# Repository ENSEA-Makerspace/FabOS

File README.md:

# FabOS
FabLab Operating System

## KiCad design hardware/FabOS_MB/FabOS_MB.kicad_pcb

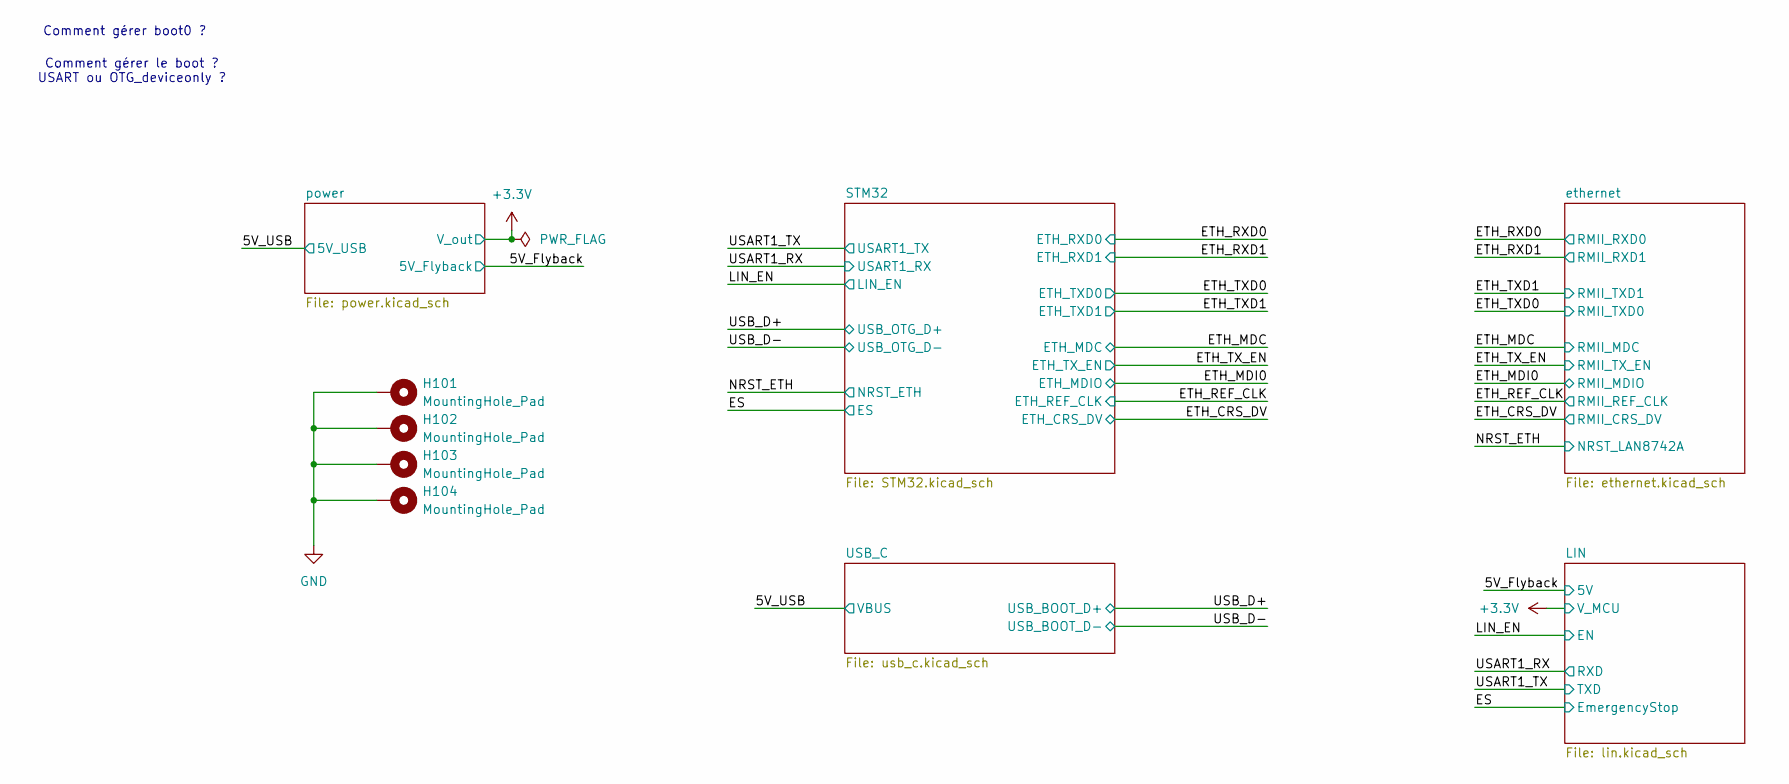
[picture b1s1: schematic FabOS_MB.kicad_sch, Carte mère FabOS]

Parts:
H101, H102, H103, H104: MountingHole_Pad; MountingHole_3.2mm_M3_Pad_Via

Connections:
GND: H101.1, H102.1, H103.1, H104.1; also elsewhere on the board

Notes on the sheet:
Comment gérer boot0 ?
Comment gérer le boot ? USART ou OTG_deviceonly ?

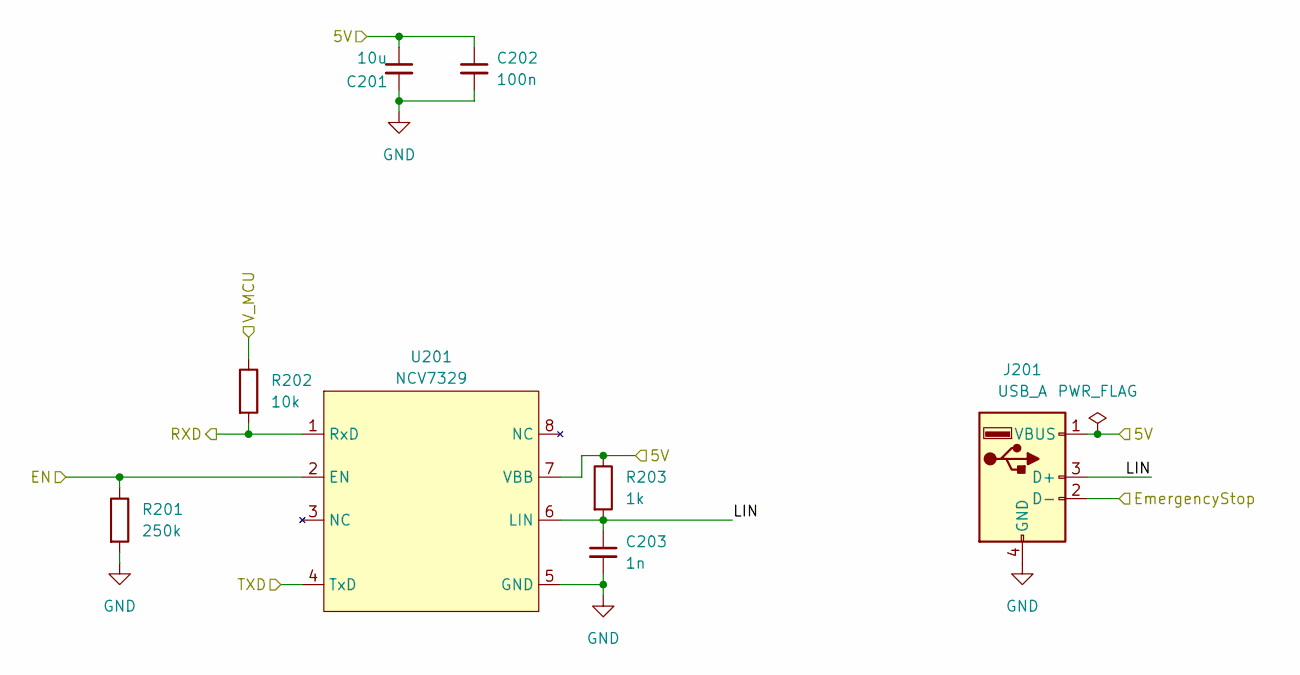
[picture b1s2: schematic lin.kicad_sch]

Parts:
C201: 10u; C_0402_1005Metric; MPN CL05A106MQ5NUNC; LCSC C15525
C202: 100n; C_0402_1005Metric; LCSC C361203
C203: 1n; C_0402_1005Metric; LCSC C92841
J201: USB_A; USB_A_Femelle; MPN 908-371A1011D10100; LCSC C42576
R201: 250k; R_0402_1005Metric; LCSC C409682
R202: 10k; R_0402_1005Metric; LCSC C25744
R203: 1k; R_0402_1005Metric; LCSC C102748
U201: NCV7329; MPN NCV7329D10R2G; LCSC C194435

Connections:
+3.3V: R202.1; also elsewhere on the board
/5V_Flyback: C201.1, C202.1, J201.1 (VBUS), R203.1, U201.7 (VBB); also elsewhere on the board
/ES: J201.2 (D-); also elsewhere on the board
/LIN/LIN: C203.1, J201.3 (D+), R203.2, U201.6 (LIN)
/LIN_EN: R201.1, U201.2 (EN); also elsewhere on the board
/USART1_RX: R202.2, U201.1 (RxD); also elsewhere on the board
/USART1_TX: U201.4 (TxD); also elsewhere on the board
GND: C201.2, C202.2, C203.2, J201.4 (GND), R201.2, U201.5 (GND); also elsewhere on the board

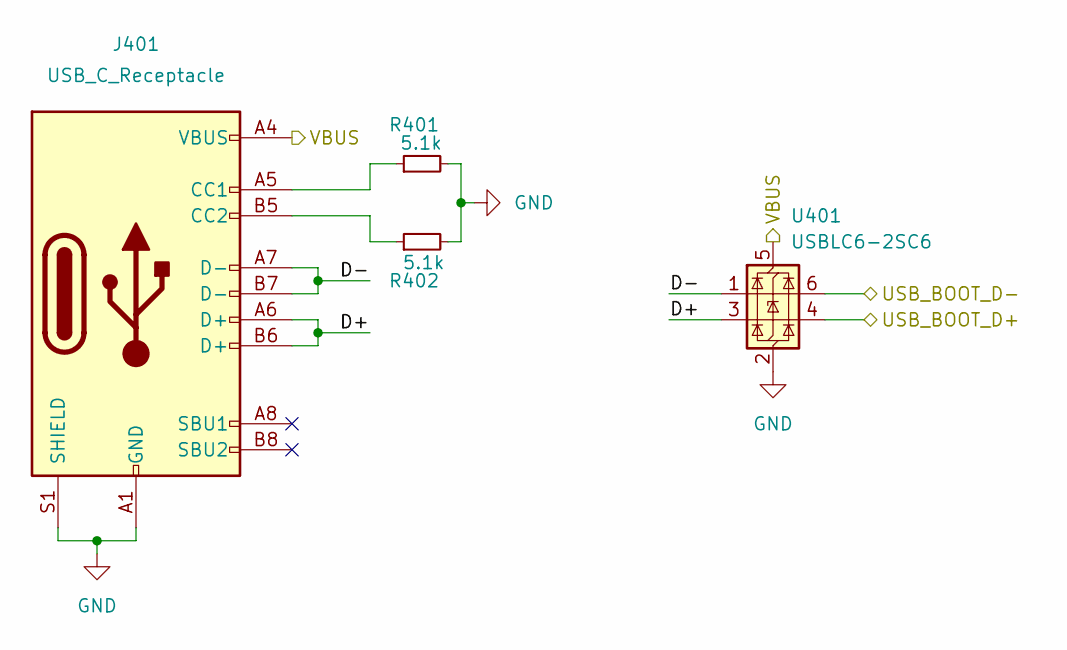
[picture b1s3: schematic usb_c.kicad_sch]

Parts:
J401: USB_C_Receptacle; USB_C_femelle_12P; MPN MC-311D; LCSC C136423
R401, R402: 5.1k; R_0402_1005Metric; LCSC C25905
U401: USBLC6-2SC6; SOT-23-6; LCSC C2827654

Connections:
/5V_USB: J401.A4 (VBUS), U401.5 (VBUS); also elsewhere on the board
/USB_C/D+: J401.A6 (D+), J401.B6 (D+), U401.3 (I/O2)
/USB_C/D-: J401.A7 (D-), J401.B7 (D-), U401.1 (I/O1)
/USB_D+: U401.4 (I/O2); also elsewhere on the board
/USB_D-: U401.6 (I/O1); also elsewhere on the board
GND: J401.A1 (GND), J401.S1 (SHIELD), R401.2, R402.2, U401.2 (GND); also elsewhere on the board
unnamed: J401.A5 (CC1), R401.1
unnamed: J401.B5 (CC2), R402.1

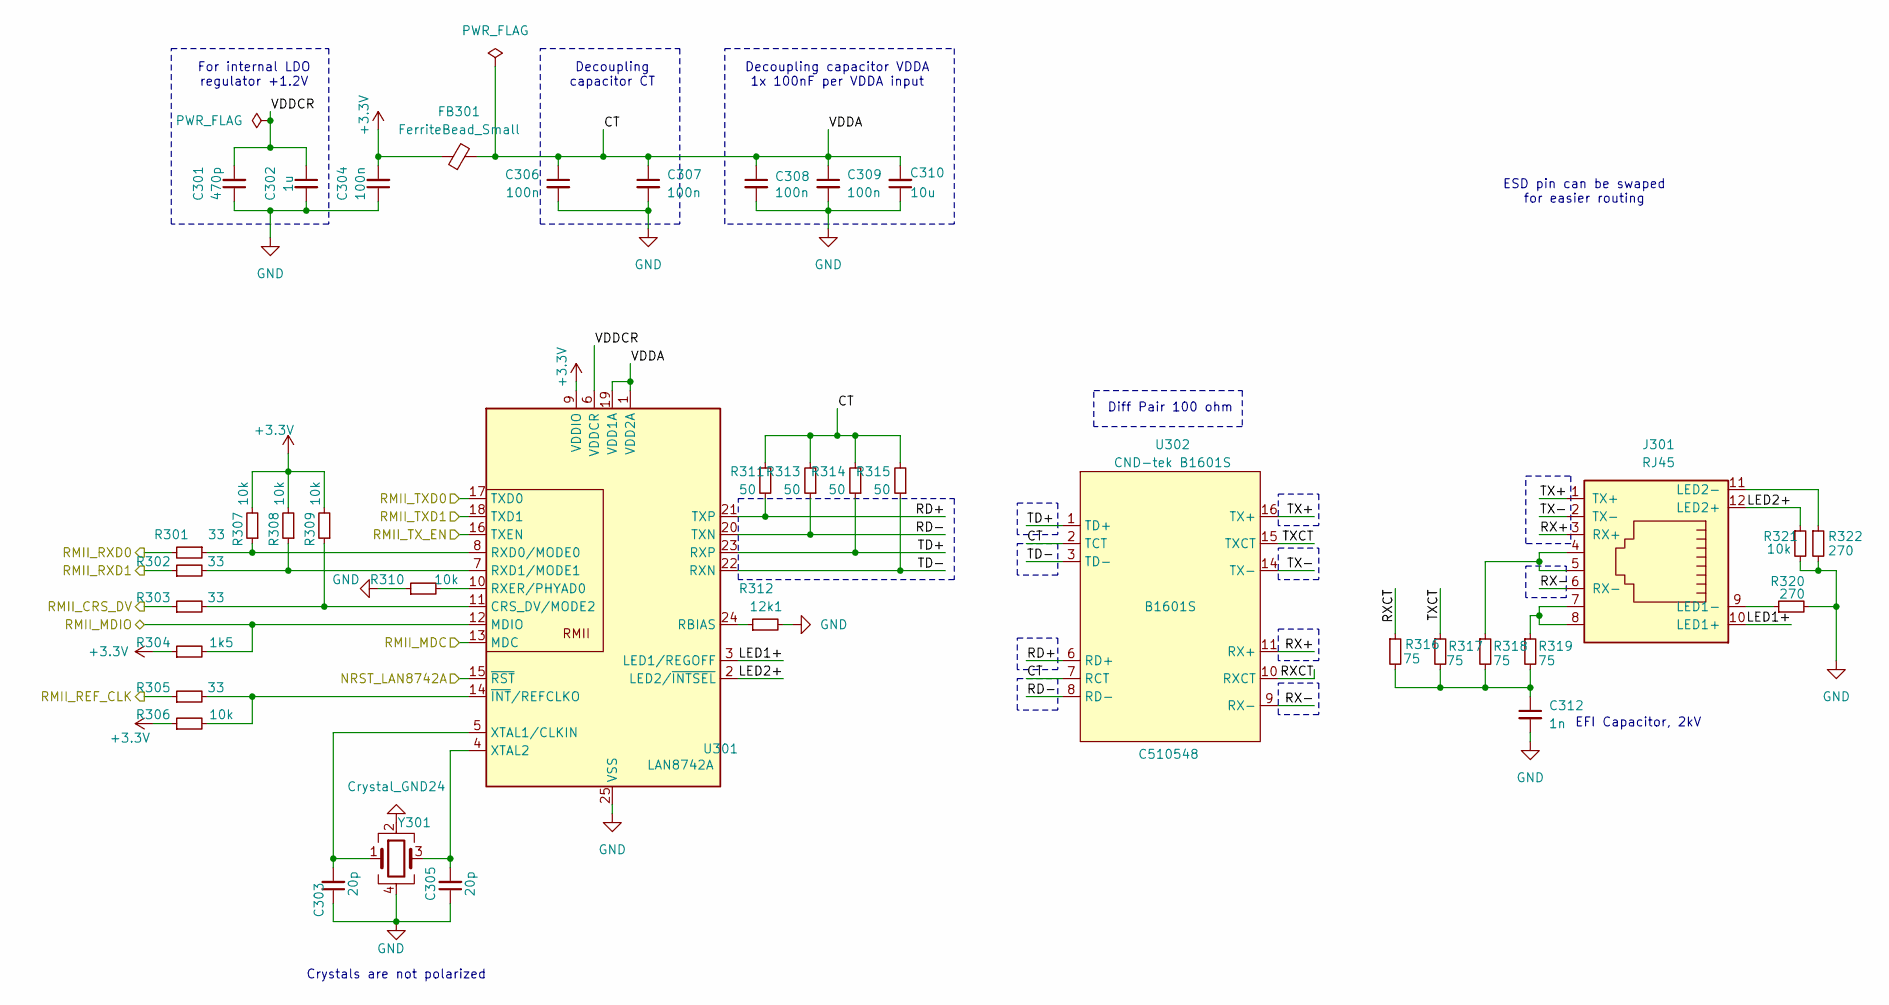
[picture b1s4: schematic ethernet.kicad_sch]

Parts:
C301: 470p; C_0402_1005Metric; LCSC C147529
C302: 1u; C_0402_1005Metric; LCSC C113791
C303, C305: 20p; C_0402_1005Metric; LCSC C107000
C304, C306, C307, C308, C309: 100n; C_0402_1005Metric; LCSC C361203
C310: 10u; C_0402_1005Metric; MPN CL05A106MQ5NUNC; LCSC C15525
C312: 1n; C_0402_1005Metric; LCSC C92841
FB301: FerriteBead_Small; L_0402_1005Metric; MPN BLM15AG102SN1D; LCSC C76883
J301: RJ45; HC-RJ45-5JAS-1-5-01; MPN HC-RJ45-5JAS-1-5-01; LCSC C20417896
R301, R302, R303, R305: 33; R_0402_1005Metric; LCSC C138002
R304: 1k5; R_0402_1005Metric; LCSC C114759
R306, R307, R308, R309, R310, R321: 10k; R_0402_1005Metric; LCSC C25744
R311, R313, R314, R315: 50; R_0402_1005Metric; LCSC C87044
R312: 12k1; R_0402_1005Metric; LCSC C3015830
R316, R317, R318, R319: 75; R_0402_1005Metric; LCSC C323700
R320, R322: 270; R_0402_1005Metric; LCSC C11429
U301: LAN8742A; VQFN-24-1EP_4x4mm_P0.5mm_EP2.5x2.5mm_ThermalVias; LCSC C621424
U302: CND-tek B1601S; CND-Tek B1601S; MPN B1601S; LCSC C510548
Y301: Crystal_GND24; Crystal_SMD_3225-4Pin_3.2x2.5mm; LCSC C7294571

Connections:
+3.3V: C304.2, FB301.1, R304.1, R306.1, R307.2, R308.2, R309.2, U301.9 (VDDIO); also elsewhere on the board
/ETH_CRS_DV: R303.1; also elsewhere on the board
/ETH_MDC: U301.13 (MDC); also elsewhere on the board
/ETH_MDI0: R304.2, U301.12 (MDIO); also elsewhere on the board
/ETH_REF_CLK: R305.1; also elsewhere on the board
/ETH_RXD0: R301.2; also elsewhere on the board
/ETH_RXD1: R302.1; also elsewhere on the board
/ETH_TXD0: U301.17 (TXD0); also elsewhere on the board
/ETH_TXD1: U301.18 (TXD1); also elsewhere on the board
/ETH_TX_EN: U301.16 (TXEN); also elsewhere on the board
/NRST_ETH: U301.15 (~RST); also elsewhere on the board
/ethernet/CT: C306.1, C307.1, C308.1, C309.1, C310.2, FB301.2, R311.1, R313.2, R314.2, R315.2, U301.1 (VDD2A), U301.19 (VDD1A), U302.2 (TCT), U302.7 (RCT)
/ethernet/LED1+: J301.10 (LED1+), U301.3 (LED1/REGOFF)
/ethernet/LED2+: J301.12 (LED2+), R321.1, U301.2 (LED2/~INTSEL)
/ethernet/RD+: R311.2, U301.21 (TXP), U302.6 (RD+)
/ethernet/RD-: R313.1, U301.20 (TXN), U302.8 (RD-)
/ethernet/RX+: J301.3 (RX+), U302.11 (RX+)
/ethernet/RX-: J301.6 (RX-), U302.9 (RX-)
/ethernet/RXCT: R316.1, U302.10 (RXCT)
/ethernet/TD+: R314.1, U301.23 (RXP), U302.1 (TD+)
/ethernet/TD-: R315.1, U301.22 (RXN), U302.3 (TD-)
/ethernet/TX+: J301.1 (TX+), U302.16 (TX+)
/ethernet/TX-: J301.2 (TX-), U302.14 (TX-)
/ethernet/TXCT: R317.1, U302.15 (TXCT)
/ethernet/VDDCR: C301.2, C302.1, U301.6 (VDDCR)
GND: C301.1, C302.2, C303.1, C304.1, C305.1, C306.2, C307.2, C308.2, C309.2, C310.1, C312.2, R310.1, R312.2, R320.2, R321.2, R322.2, U301.25 (VSS), Y301.2, Y301.4; also elsewhere on the board
unnamed: C312.1, R316.2, R317.2, R318.2, R319.2
unnamed: J301.9 (LED1-), R320.1
unnamed: J301.11 (LED2-), R322.1
unnamed: J301.4, J301.5, R318.1
unnamed: J301.7, J301.8, R319.1
unnamed: R303.2, R309.1, U301.11 (CRS_DV/MODE2)
unnamed: R312.1, U301.24 (RBIAS)
unnamed: R301.1, R307.1, U301.8 (RXD0/MODE0)
unnamed: R302.2, R308.1, U301.7 (RXD1/MODE1)
unnamed: R310.2, U301.10 (RXER/PHYAD0)
unnamed: C303.2, U301.5 (XTAL1/CLKIN), Y301.1
unnamed: C305.2, U301.4 (XTAL2), Y301.3
unnamed: R305.2, R306.2, U301.14 (~INT/REFCLKO)

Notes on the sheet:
ESD pin can be swaped for easier routing
Decoupling capacitor CT
For internal LDO regulator +1.2V
Crystals are not polarized
EFI Capacitor, 2kV
Decoupling capacitor VDDA 1x 100nF per VDDA input
Diff Pair 100 ohm

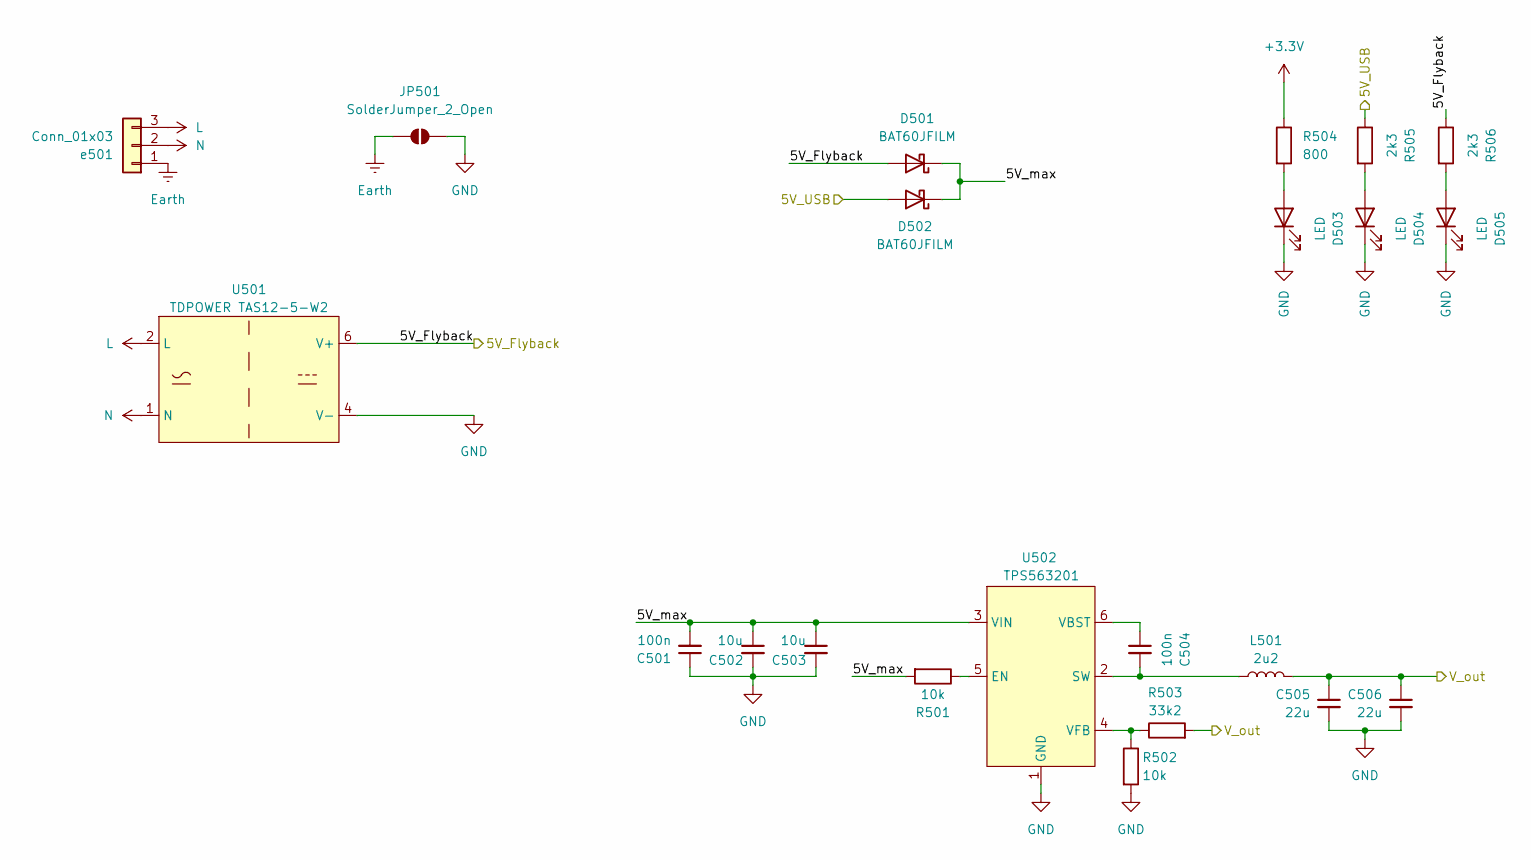
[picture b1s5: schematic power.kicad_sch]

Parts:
C501, C504: 100n; C_0402_1005Metric; LCSC C361203
C502, C503: 10u; C_0402_1005Metric; MPN CL05A106MQ5NUNC; LCSC C15525
C505, C506: 22u; C_0603_1608Metric; MPN CL10A226MQ8NRNC; LCSC C59461
D501, D502: BAT60JFILM; D_SOD-323; LCSC C154819
D503, D504, D505: LED; D_0402_1005Metric; LCSC C397046
JP501: SolderJumper_2_Open; SolderJumper-2_P1.3mm_Open_TrianglePad1.0x1.5mm
L501: 2u2; L_1206_3216Metric; LCSC C139249
R501, R502: 10k; R_0402_1005Metric; LCSC C25744
R503: 33k2; R_0402_1005Metric; LCSC C162863
R504: 800; R_0402_1005Metric; LCSC C103166
R505, R506: 2k3; R_0402_1005Metric; LCSC C100323
U501: TDPOWER TAS12-5-W2; TD POWER TAS12-5-W2; MPN TAS12-5-W2; LCSC C5354760
U502: TPS563201; MPN TPS563201DDCR; LCSC C116592
e501: Conn_01x03; PhoenixContact_MC_1,5_3-G-5.08_1x03_P5.08mm_Horizontal; LCSC C8377

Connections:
+3.3V: C505.1, C506.1, L501.1, R503.2, R504.1; also elsewhere on the board
/5V_Flyback: D501.2 (A), R506.1, U501.6 (V+); also elsewhere on the board
/5V_USB: D502.2 (A), R505.1; also elsewhere on the board
/power/5V_max: C501.2, C502.1, C503.1, D501.1 (K), D502.1 (K), R501.2, U502.3 (VIN)
Earth: JP501.1 (A), e501.1
GND: C501.1, C502.2, C503.2, C505.2, C506.2, D503.1 (K), D504.1 (K), D505.1 (K), JP501.2 (B), R502.2, U501.4 (V-), U502.1 (GND); also elsewhere on the board
L: U501.2 (L), e501.3
N: U501.1 (N), e501.2
unnamed: D503.2 (A), R504.2
unnamed: D504.2 (A), R505.2
unnamed: D505.2 (A), R506.2
unnamed: R501.1, U502.5 (EN)
unnamed: C504.2, L501.2, U502.2 (SW)
unnamed: C504.1, U502.6 (VBST)
unnamed: R502.1, R503.1, U502.4 (VFB)

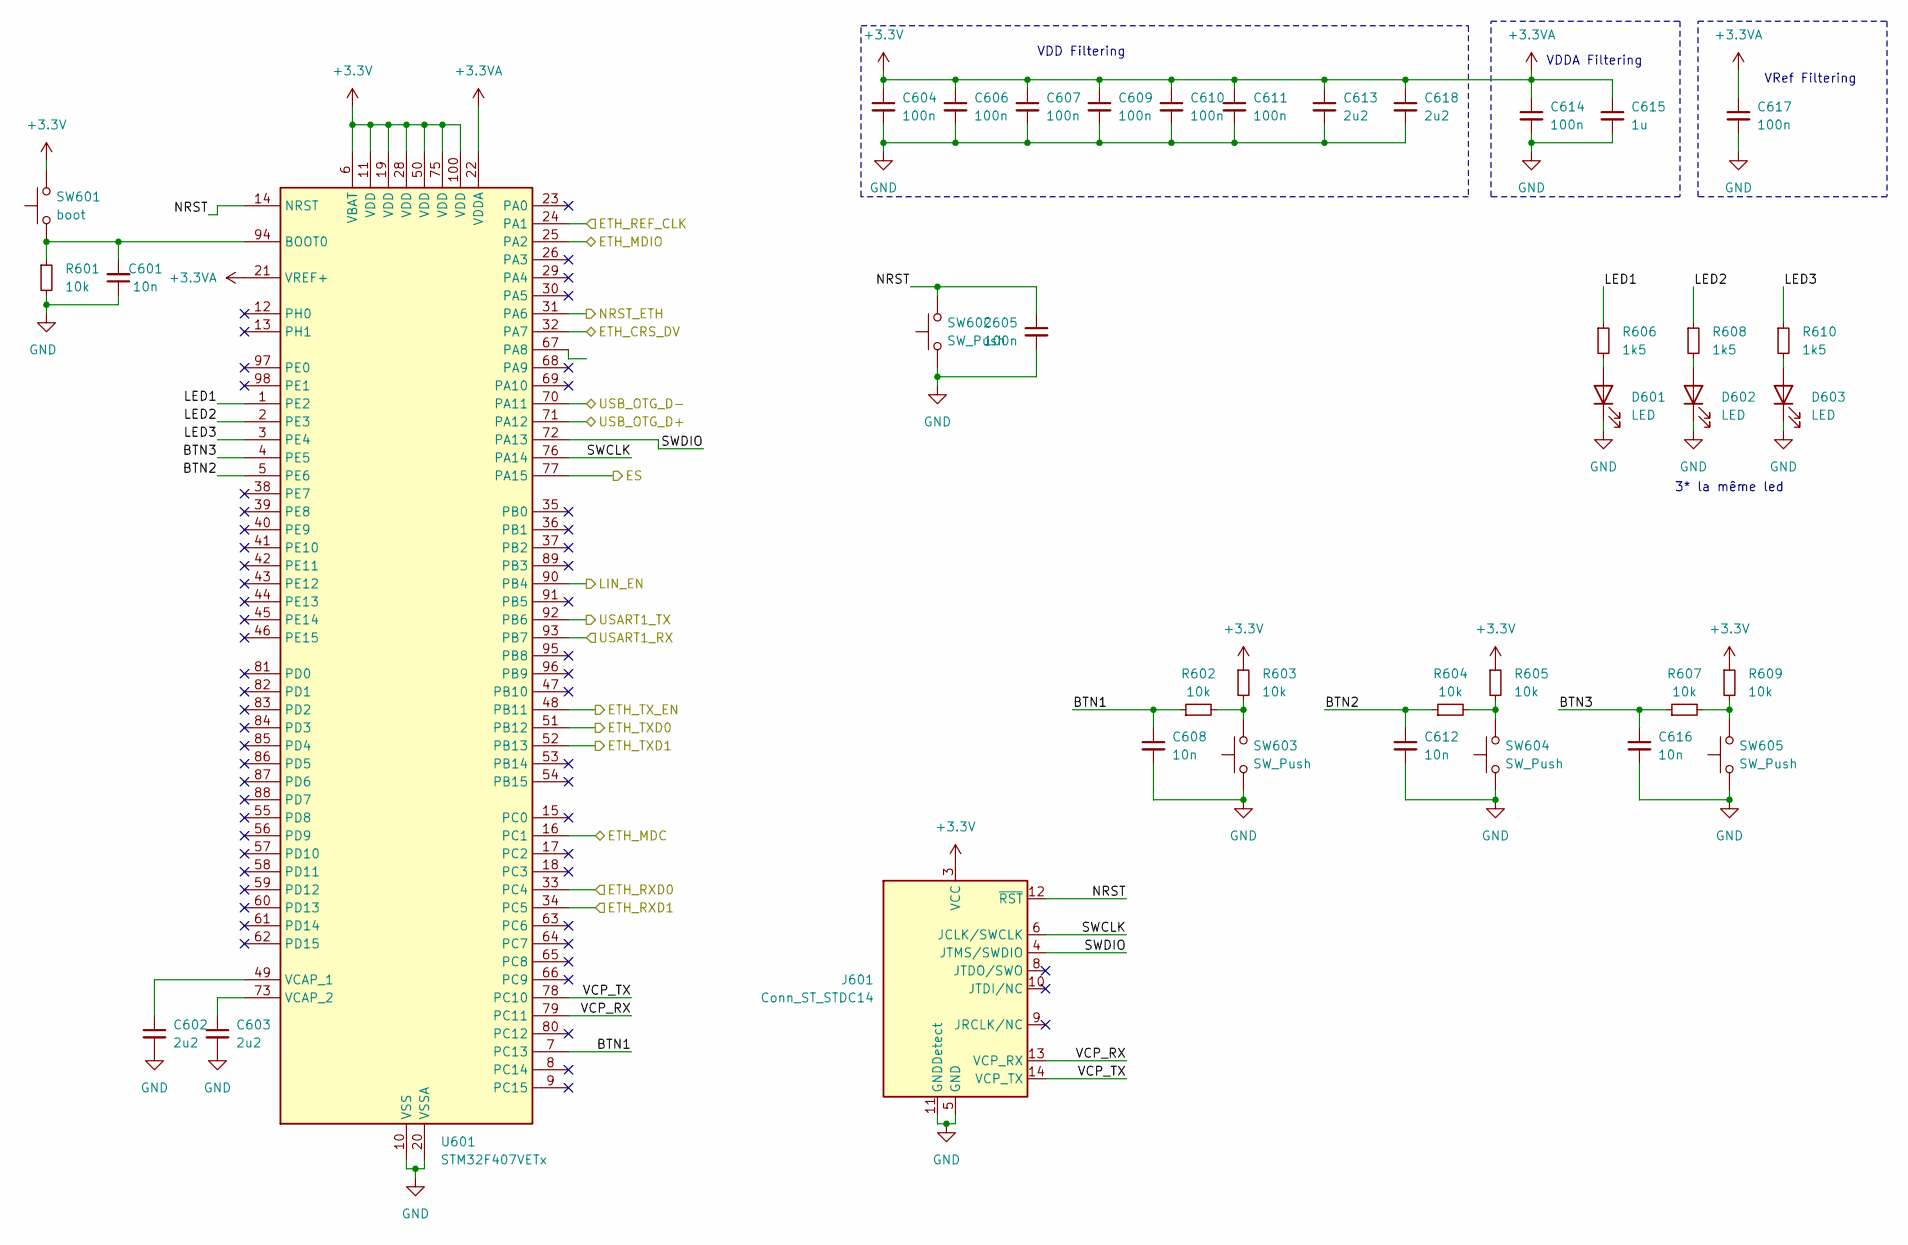
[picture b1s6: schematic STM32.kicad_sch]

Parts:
C601, C608, C612, C616: 10n; C_0402_1005Metric; LCSC C576726
C602, C603, C613, C618: 2u2; C_0402_1005Metric; MPN CL05A225MQ5NSNC; LCSC C12530
C604, C605, C606, C607, C609, C610, C611, C614, C617: 100n; C_0402_1005Metric; LCSC C361203
C615: 1u; C_0402_1005Metric; LCSC C113791
D601, D602, D603: LED; D_0402_1005Metric; LCSC C510301
J601: Conn_ST_STDC14; PinHeader_2x07_P1.27mm_Vertical_SMD; LCSC C3975190
R601, R602, R603, R604, R605, R607, R609: 10k; R_0402_1005Metric; LCSC C25744
R606, R608, R610: 1k5; R_0402_1005Metric; LCSC C114759
SW601: boot; SW_SPST_B3U-3000P; MPN B3U-3000P; LCSC C963349
SW602: SW_Push; SW_SPST_B3U-3000P; MPN B3U-3000P; LCSC C963349
SW603, SW604, SW605: SW_Push; SW_Push_1P1T_NO_6x6mm_H9.5mm; LCSC C5127964
U601: STM32F407VETx; LQFP-100_14x14mm_P0.5mm; LCSC C390804

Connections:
+3.3V: C604.1, C606.1, C607.1, C609.1, C610.1, C611.1, C613.1, C614.1, C615.1, C617.1, C618.1, J601.3 (VCC), R603.1, R605.1, R609.1, SW601.2, U601.6 (VBAT), U601.11 (VDD), U601.19 (VDD), U601.21 (VREF+), U601.22 (VDDA), U601.28 (VDD), U601.50 (VDD), U601.75 (VDD), U601.100 (VDD); also elsewhere on the board
/ES: U601.77 (PA15); also elsewhere on the board
/ETH_CRS_DV: U601.32 (PA7); also elsewhere on the board
/ETH_MDC: U601.16 (PC1); also elsewhere on the board
/ETH_MDI0: U601.25 (PA2); also elsewhere on the board
/ETH_REF_CLK: U601.24 (PA1); also elsewhere on the board
/ETH_RXD0: U601.33 (PC4); also elsewhere on the board
/ETH_RXD1: U601.34 (PC5); also elsewhere on the board
/ETH_TXD0: U601.51 (PB12); also elsewhere on the board
/ETH_TXD1: U601.52 (PB13); also elsewhere on the board
/ETH_TX_EN: U601.48 (PB11); also elsewhere on the board
/LIN_EN: U601.90 (PB4); also elsewhere on the board
/NRST_ETH: U601.31 (PA6); also elsewhere on the board
/STM32/BTN1: C608.1, R602.1, U601.7 (PC13)
/STM32/BTN2: C612.1, R604.1, U601.5 (PE6)
/STM32/BTN3: C616.1, R607.1, U601.4 (PE5)
/STM32/LED1: R606.1, U601.1 (PE2)
/STM32/LED2: R608.1, U601.2 (PE3)
/STM32/LED3: R610.1, U601.3 (PE4)
/STM32/NRST: C605.1, J601.12 (~RST), SW602.2, U601.14 (NRST)
/STM32/SWCLK: J601.6 (JCLK/SWCLK), U601.76 (PA14)
/STM32/SWDIO: J601.4 (JTMS/SWDIO), U601.72 (PA13)
/STM32/VCP_RX: J601.13 (VCP_RX), U601.79 (PC11)
/STM32/VCP_TX: J601.14 (VCP_TX), U601.78 (PC10)
/USART1_RX: U601.93 (PB7); also elsewhere on the board
/USART1_TX: U601.92 (PB6); also elsewhere on the board
/USB_D+: U601.71 (PA12); also elsewhere on the board
/USB_D-: U601.70 (PA11); also elsewhere on the board
GND: C601.1, C602.2, C603.2, C604.2, C605.2, C606.2, C607.2, C608.2, C609.2, C610.2, C611.2, C612.2, C613.2, C614.2, C615.2, C616.2, C617.2, C618.2, D601.1 (K), D602.1 (K), D603.1 (K), J601.5 (GND), J601.7 (GND), J601.11 (GNDDetect), R601.2, SW602.1, SW603.1, SW604.1, SW605.1, U601.10 (VSS), U601.20 (VSSA), U601.27 (VSS), U601.74 (VSS), U601.99 (VSS); also elsewhere on the board
unnamed: D601.2 (A), R606.2
unnamed: D602.2 (A), R608.2
unnamed: D603.2 (A), R610.2
unnamed: R602.2, R603.2, SW603.2
unnamed: R604.2, R605.2, SW604.2
unnamed: R607.2, R609.2, SW605.2
unnamed: C601.2, R601.1, SW601.1, U601.94 (BOOT0)
unnamed: C602.1, U601.49 (VCAP_1)
unnamed: C603.1, U601.73 (VCAP_2)

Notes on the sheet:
VDDA Filtering
VRef Filtering
3* la même led
VDD Filtering

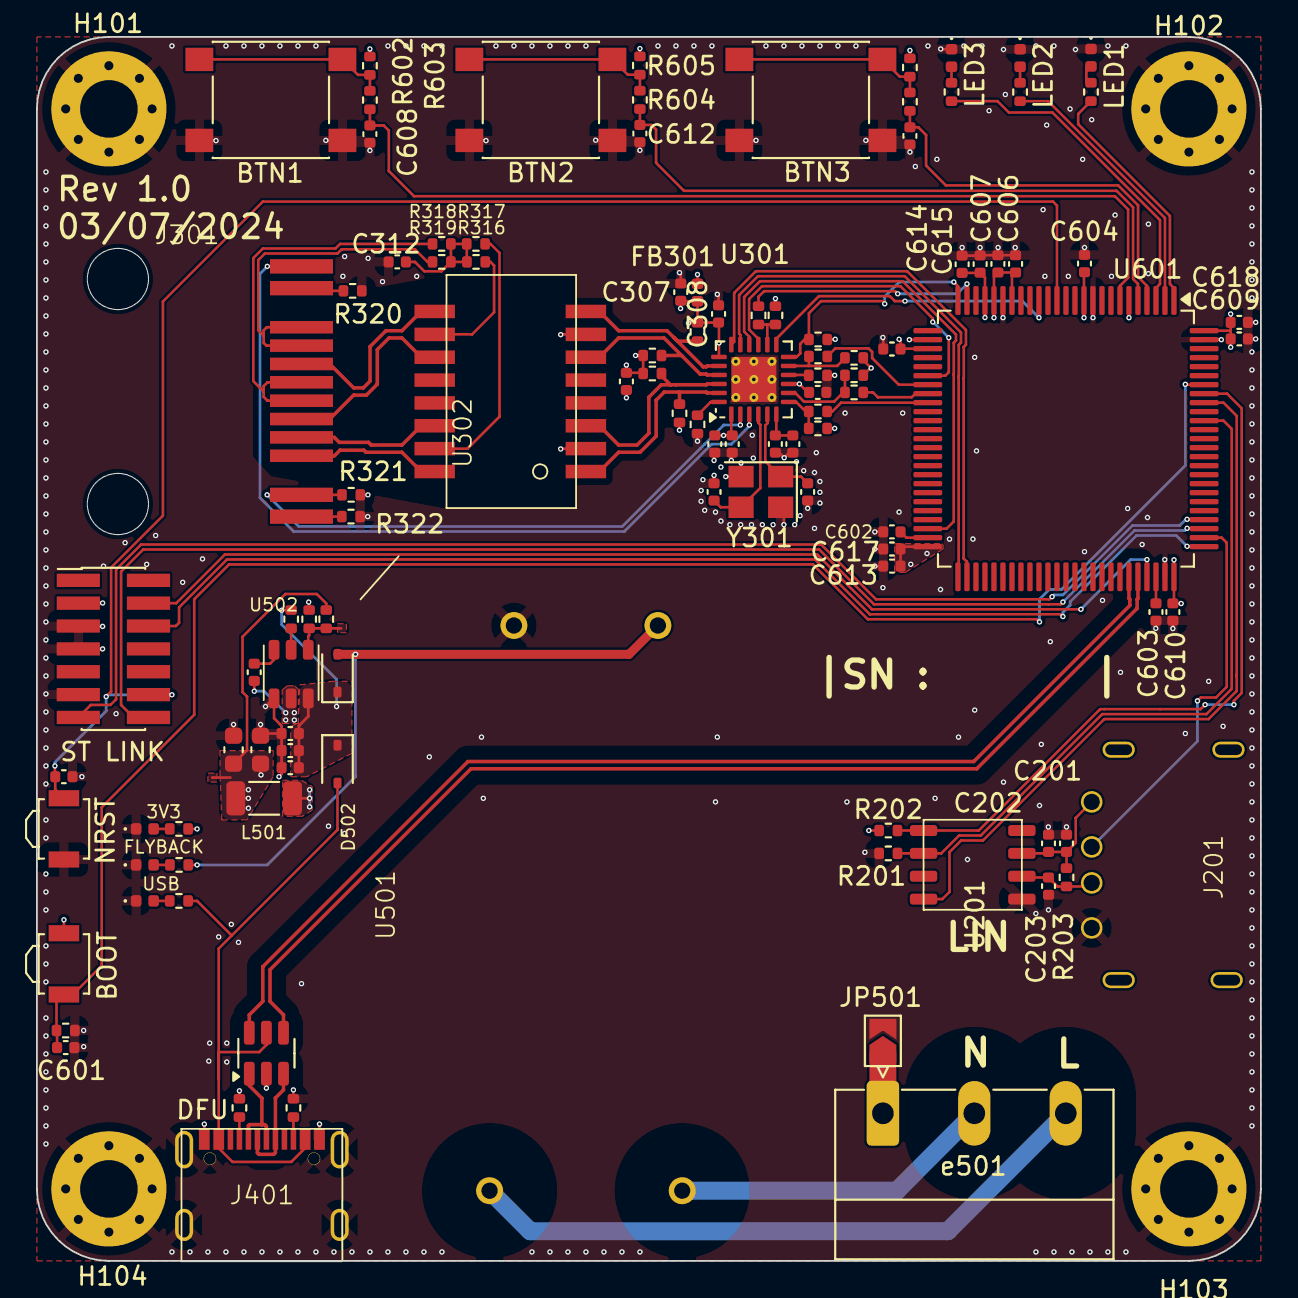
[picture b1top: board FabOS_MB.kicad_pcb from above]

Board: 4 copper layers, 68.0 x 68.0 mm, 114 parts (0 on the bottom side), 83 nets.

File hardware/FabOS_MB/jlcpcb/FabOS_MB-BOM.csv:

Comment,Designator,Footprint,JLCPCB Part #,Remplacement
10u ,"C201, C310, C502, C503",C0402_1005Metric,C15525,
100n ,"C202, C304, C306, C307, C308, C309, C501, C504, C604, C605, C606, C607, C609, C610, C611, C614, C617",C0402_1005Metric,C361203 ,
1n ,"C203, C312",C0402_1005Metric,C92841,
470p ,C301,C0402_1005Metric,C147529,
1u ,"C302, C615",C0402_1005Metric,C113791,
20p ,"C303, C305",C0402_1005Metric,C107000,
22u ,"C505, C506",C0603_1608Metric,C59461,
10n ,"C601, C608, C612, C616",C0402_1005Metric,C576726,
2u2 ,"C602, C603, C613, C618",C0402_1005Metric,C12530 ,
BAT60JFILM ,"D501, D502",D_SOD-323,C3975190,
LED ,"D601, D602, D603",D_0402_1005Metric,C510301,red
LED ,"D503, D504, D505",D_0402_1005Metric,C397046,white
FerriteBead_Small ,FB301,L_0402_1005Metric,C76883 ,
USB_A ,J201,USB_A_Femelle,C42576,
RJ45 ,J301,HC-RJ45-5JAS-1-5-01,C20417896,
USB_C_Receptacle ,J401,USB_C_femelle_12P,C136423,
Conn_ST_STDC14 ,J601,PinHeader_2x07_P1.27mm_Vertical_SMD,C3975190,
2u2 ,L501,L_1206_3216Metric,C139249,
249k,R201,R0402_1005Metric,C409682,249k
10k ,"R202, R501, R502",R0402_1005Metric,C25744,
1k ,R203,R0402_1005Metric,C102748,
33,"R301, R302, R303, R305",R0402_1005Metric,C138002,
1k5 ,"R304, R606, R608, R610",R0402_1005Metric,C114759,
10k ,"R306, R307, R308, R309, R310, R321, R601, R602, R603, R604, R605, R607, R609",R0402_1005Metric,C25744,
"49,9","R311, R313, R314, R315",R0402_1005Metric,C87044,
12k1 ,R312,R0402_1005Metric,C3015830,
75,"R316, R317, R318, R319",R0402_1005Metric,C323700,
270,"R320, R322",R0402_1005Metric,C11429,
5.1k ,"R401, R402",R0402_1005Metric,C25905,
33k,R503,R0402_1005Metric,C162863,
820,R504,R0402_1005Metric,C103166,820
2k3 ,"R505, R506",R0402_1005Metric,C100323,
boot ,SW601,SW_SPST_B3U-3000P,C963349,
SW_Push ,SW602,SW_SPST_B3U-3000P,C963349,
SW_Push ,"SW603, SW604, SW605",SW_Push_1P1T_NO_6x6mm_H9.5mm,C5127964,
NCV7329 ,U201,NCV7329,C194435,TJA1029T/20/1J 
LAN8742A ,U301,VQFN-24-1EP_4x4mm_P0.5mm_EP2.5x2.5mm_ThermalVias,C621424,
CND-tek B1601S ,U302,CND-Tek B1601S,C510548,
USBLC6-2SC6 ,U401,SOT-23-6,C2827654,
TDPOWER TAS12-5-W2 ,U501,TD POWER TAS12-5-W2,C5354760,
TPS563201 ,U502,TPS563201,C116592,
STM32F407VETx ,U601,LQFP-100_14x14mm_P0.5mm,C28730,
Crystal_GND24 ,Y301,Crystal_SMD_3225-4Pin_3.2x2.5mm,C390804,
Conn_01x03 ,e501,"PhoenixContact_MC1,5_3-G-5.08_1x03_P5.08mm_Horizontal",C8377,

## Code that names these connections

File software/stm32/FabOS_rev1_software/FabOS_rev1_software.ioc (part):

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Mcu.Name=STM32F407V(E-G)Tx
Mcu.Package=LQFP100
Mcu.UserName=STM32F407VETx
PA1.Mode=RMII
PA1.Signal=ETH_REF_CLK
PA13.Mode=Serial_Wire
PA13.Signal=SYS_JTMS-SWDIO
PA14.Mode=Serial_Wire
PA14.Signal=SYS_JTCK-SWCLK
PA15.GPIOParameters=GPIO_Label
PA15.GPIO_Label=EMERGENCY_STOP
PA15.Signal=GPIO_Output
PA2.Mode=RMII
PA2.Signal=ETH_MDIO
PA6.GPIOParameters=GPIO_Label
PA6.GPIO_Label=NRST_ETH
PA6.Signal=GPIO_Output
PA7.Mode=RMII
PA7.Signal=ETH_CRS_DV
PB11.Mode=RMII
PB11.Signal=ETH_TX_EN
PB12.Mode=RMII
PB12.Signal=ETH_TXD0
PB13.Mode=RMII
PB13.Signal=ETH_TXD1
PB4.GPIOParameters=GPIO_Label
PB4.GPIO_Label=LIN_EN
PB4.Signal=GPIO_Output
PB6.GPIOParameters=GPIO_Label
PB6.GPIO_Label=UART_LIN_TX
PB6.Mode=Asynchronous
PB6.Signal=USART1_TX
PB7.GPIOParameters=GPIO_Label
PB7.GPIO_Label=UART_LIN_RX
PB7.Mode=Asynchronous
PB7.Signal=USART1_RX
PC1.Mode=RMII
PC1.Signal=ETH_MDC
PC10.GPIOParameters=GPIO_Label
PC10.GPIO_Label=VCP_RX
PC10.Mode=Asynchronous
PC10.Signal=UART4_TX
PC11.GPIOParameters=GPIO_Label
PC11.GPIO_Label=VCP_RX
PC11.Mode=Asynchronous
PC11.Signal=UART4_RX
PC13-ANTI_TAMP.GPIOParameters=GPIO_Label
PC13-ANTI_TAMP.GPIO_Label=USR_BTN_1
PC13-ANTI_TAMP.Signal=GPXTI13
PC4.Mode=RMII
PC4.Signal=ETH_RXD0
PC5.Mode=RMII
PC5.Signal=ETH_RXD1
PE2.GPIOParameters=GPIO_Label
PE2.GPIO_Label=USR_LED_1
PE2.Signal=GPIO_Output
PE3.GPIOParameters=GPIO_Label
PE3.GPIO_Label=USR_LED_2
PE3.Signal=GPIO_Output
PE4.GPIOParameters=GPIO_Label
PE4.GPIO_Label=USR_LED_3
PE4.Signal=GPIO_Output
PE5.GPIOParameters=GPIO_Label
PE5.GPIO_Label=USR_BTN_3
PE5.Signal=GPXTI5
PE6.GPIOParameters=GPIO_Label
PE6.GPIO_Label=USR_BTN_2
PE6.Signal=GPXTI6
PH0-OSC_IN.Mode=HSE-External-Oscillator
PH0-OSC_IN.Signal=RCC_OSC_IN
PH1-OSC_OUT.Mode=HSE-External-Oscillator
PH1-OSC_OUT.Signal=RCC_OSC_OUT
RCC.HSE_VALUE=25000000
RCC.SYSCLKFreq_VALUE=48000000
RCC.SYSCLKSource=RCC_SYSCLKSOURCE_PLLCLK
board=custom
